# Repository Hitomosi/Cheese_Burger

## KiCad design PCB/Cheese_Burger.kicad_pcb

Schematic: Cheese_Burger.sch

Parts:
J1: BH-14SG; PinHeader_2x07_P2.54mm_Vertical

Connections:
3.3V: J1.13; also elsewhere on the board
3.3VA: J1.14; also elsewhere on the board
/IR_LED1/IR_LED_IN: J1.2; also elsewhere on the board
/IR_LED2/IR_LED_IN: J1.4; also elsewhere on the board
/IR_Sensor1/IR_SENSOR_OUT: J1.6; also elsewhere on the board
/IR_Sensor2/IR_SENSOR_OUT: J1.8; also elsewhere on the board
/IR_Sensor3/IR_SENSOR_OUT: J1.10; also elsewhere on the board
/IR_Sensor4/IR_SENSOR_OUT: J1.12; also elsewhere on the board
BATT: J1.1, J1.3, J1.5; also elsewhere on the board
GND: J1.7, J1.9, J1.11; also elsewhere on the board

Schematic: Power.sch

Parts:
C1: 10u; C_Disc_D5.0mm_W2.5mm_P5.00mm
C2: 0.1u; C_Disc_D5.0mm_W2.5mm_P5.00mm
D1: LED(OSNG5113A); LED_D5.0mm
F1: MF-RX160; RF-RX160
J2: JST_XA_1x2; JST_XH_B02B-XH-A_1x02_P2.50mm_Vertical
L1: 100u; L_Axial_L7.0mm_D3.3mm_P10.16mm_Horizontal_Fastron_MICC
Q1: 2SK4017; SIPAK_Vertical
R1: 100k; R_Axial_DIN0207_L6.3mm_D2.5mm_P7.62mm_Horizontal
R2: 68; R_Axial_DIN0207_L6.3mm_D2.5mm_P7.62mm_Horizontal
R3: 10; R_Axial_DIN0207_L6.3mm_D2.5mm_P7.62mm_Horizontal
R4, R5: 1k 1%; R_Axial_DIN0207_L6.3mm_D2.5mm_P7.62mm_Horizontal
SW1: SW_SPDT; PinHeader_1x03_P2.54mm_Vertical
U1: R-78E3.3-0.5; Converter_DCDC_RECOM_R-78E-0.5_THT

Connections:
1.65V: C2.1, R4.2, R5.1; also elsewhere on the board
3.3V: R2.1, R3.2, U1.3 (OUT); also elsewhere on the board
3.3VA: C1.1, L1.1, R4.1; also elsewhere on the board
BATT: Q1.2, U1.1 (IN); also elsewhere on the board
GND: C1.2, C2.2, D1.1, J2.2, R5.2, SW1.2, SW1.3, U1.2 (GND); also elsewhere on the board
unnamed: D1.2, R2.2
unnamed: F1.1, Q1.3, R1.1
unnamed: F1.2, J2.1
unnamed: L1.2, R3.1
unnamed: Q1.1, R1.2, SW1.1

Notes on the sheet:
11.1V

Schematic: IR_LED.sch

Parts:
D4, D5: LED_ALT; LED_D5.0mm_Horizontal_O6.35mm_Z9.0mm
Q3: 2SK2796; SIPAK_Vertical
R9: 10k; R_Axial_DIN0207_L6.3mm_D2.5mm_P7.62mm_Horizontal
R10: 10; R_Axial_DIN0207_L6.3mm_D2.5mm_P7.62mm_Horizontal
R11: 33 1/2W 1%; R_Axial_DIN0207_L6.3mm_D2.5mm_P7.62mm_Horizontal
U2: NJM2742D; DIP-8_W7.62mm_Socket

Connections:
/IR_LED1/IR_LED_IN: R9.2, U2.5; also elsewhere on the board
/IR_LED2/IR_LED_IN: U2.3; also elsewhere on the board
BATT: D4.2, U2.8; also elsewhere on the board
GND: R9.1, R11.1, U2.4; also elsewhere on the board
unnamed: D4.1, D5.2
unnamed: D5.1, Q3.2
unnamed 29: U2.2; also elsewhere on the board
unnamed: Q3.1, R10.1
unnamed: Q3.3, R11.2, U2.6
unnamed 32: U2.1; also elsewhere on the board
unnamed: R10.2, U2.7

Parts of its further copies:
D2, D3: LED_ALT; LED_D5.0mm_Horizontal_O6.35mm_Z9.0mm
Q2: 2SK2796; SIPAK_Vertical
R6: 10k; R_Axial_DIN0207_L6.3mm_D2.5mm_P7.62mm_Horizontal
R7: 10; R_Axial_DIN0207_L6.3mm_D2.5mm_P7.62mm_Horizontal
R8: 33 1/2W 1%; R_Axial_DIN0207_L6.3mm_D2.5mm_P7.62mm_Horizontal

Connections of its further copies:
/IR_LED2/IR_LED_IN: R6.2; also elsewhere on the board
BATT: D2.2; also elsewhere on the board
GND: R6.1, R8.1; also elsewhere on the board
unnamed: D2.1, D3.2
unnamed: D3.1, Q2.2
unnamed: Q2.1, R7.1
unnamed 29: Q2.3, R8.2; also elsewhere on the board
unnamed 32: R7.2; also elsewhere on the board

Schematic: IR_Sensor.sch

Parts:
C3, C4: 22p; C_Disc_D5.0mm_W2.5mm_P5.00mm
D6: D_Photo_ALT; LED_D5.0mm_Horizontal_O3.81mm_Z3.0mm
R12, R13: 220k; R_Axial_DIN0207_L6.3mm_D2.5mm_P7.62mm_Horizontal
U3: NJU7072D; DIP-8_W7.62mm_Socket

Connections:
1.65V: U3.3, U3.5; also elsewhere on the board
3.3VA: D6.1, U3.8; also elsewhere on the board
/IR_Sensor1/IR_SENSOR_OUT: C4.1, R13.1, U3.1; also elsewhere on the board
/IR_Sensor2/IR_SENSOR_OUT: U3.7; also elsewhere on the board
GND: R12.1, U3.4; also elsewhere on the board
unnamed: C3.1, C4.2, R13.2, U3.2
unnamed: C3.2, D6.2, R12.2
unnamed 13: U3.6; also elsewhere on the board

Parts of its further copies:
C5, C6, C7, C8, C9, C10: 22p; C_Disc_D5.0mm_W2.5mm_P5.00mm
D7, D8, D9: D_Photo_ALT; LED_D5.0mm_Horizontal_O3.81mm_Z3.0mm
R14, R15, R16, R17, R18, R19: 220k; R_Axial_DIN0207_L6.3mm_D2.5mm_P7.62mm_Horizontal
U4: NJU7072D; DIP-8_W7.62mm_Socket

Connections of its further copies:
1.65V: U4.3, U4.5; also elsewhere on the board
3.3VA: D7.1, D8.1, D9.1, U4.8; also elsewhere on the board
/IR_Sensor2/IR_SENSOR_OUT: C6.1, R15.1; also elsewhere on the board
/IR_Sensor3/IR_SENSOR_OUT: C8.1, R17.1, U4.1; also elsewhere on the board
/IR_Sensor4/IR_SENSOR_OUT: C10.1, R19.1, U4.7; also elsewhere on the board
GND: R14.1, R16.1, R18.1, U4.4; also elsewhere on the board
unnamed 13: C5.1, C6.2, R15.2; also elsewhere on the board
unnamed: C5.2, D7.2, R14.2
unnamed: C7.1, C8.2, R17.2, U4.2
unnamed: C7.2, D8.2, R16.2
unnamed: C9.2, D9.2, R18.2
unnamed: C9.1, C10.2, R19.2, U4.6

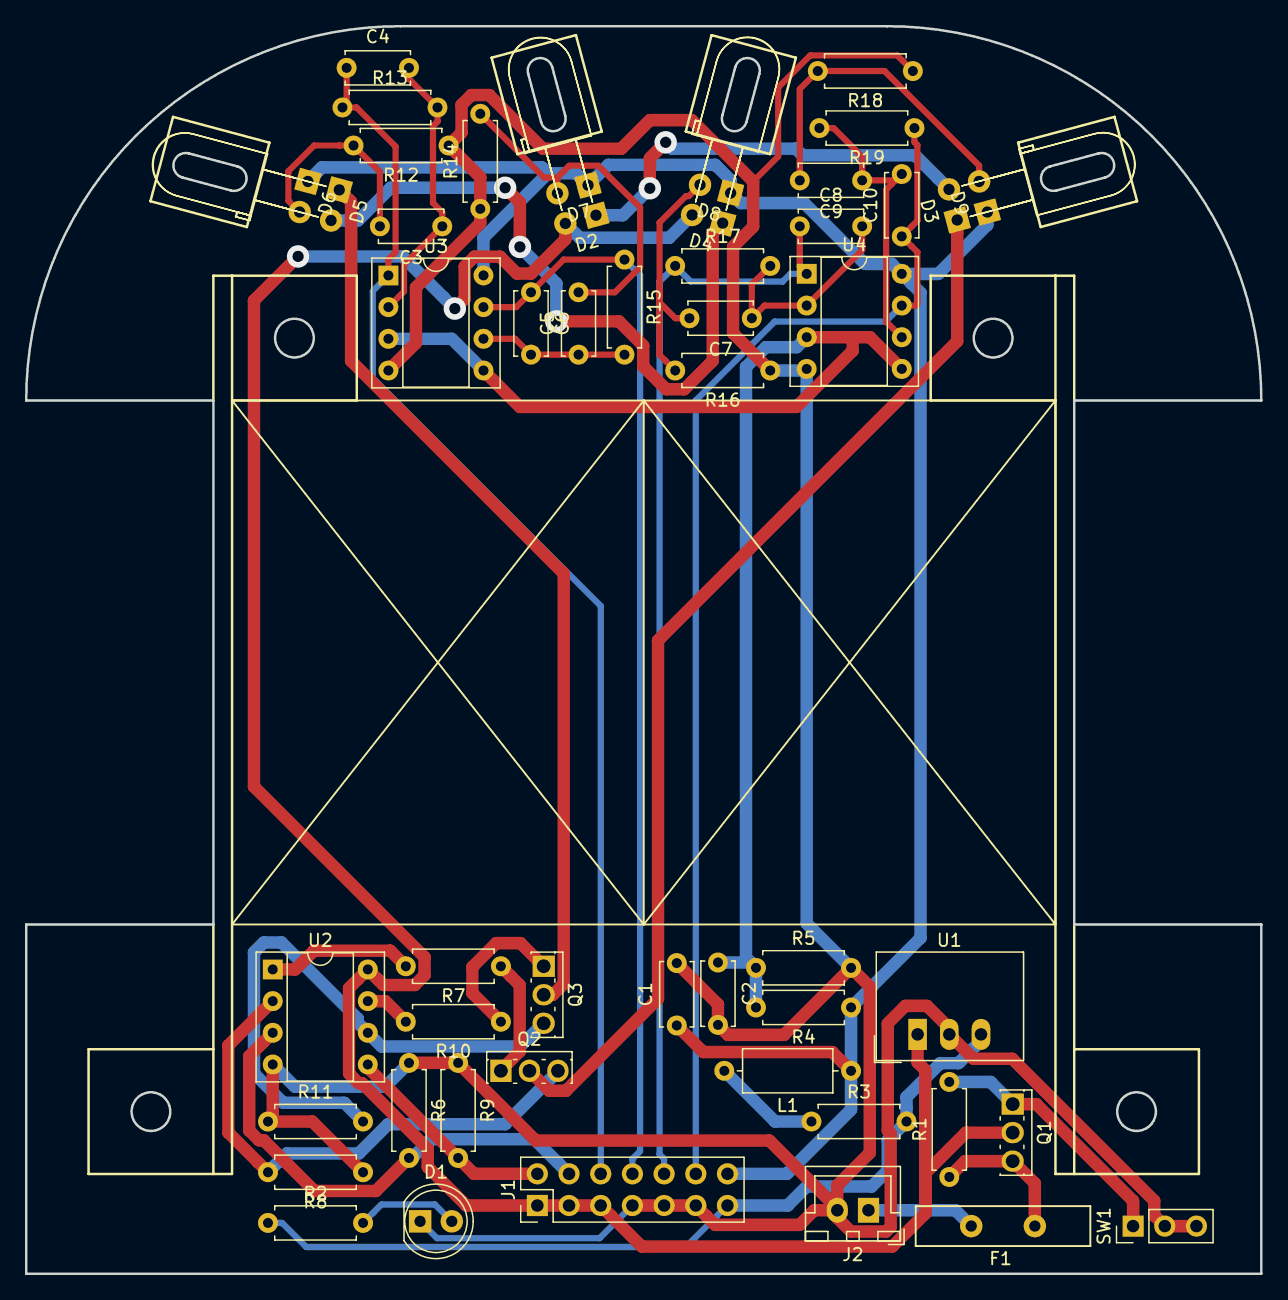
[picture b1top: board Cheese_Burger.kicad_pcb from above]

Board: 2 copper layers, 99.0 x 100.0 mm, 50 parts (0 on the bottom side), 34 nets.

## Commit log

2020-05-09 DXFを追加、部品配置を開始
2020-05-09 回路図を修正
2020-05-15 下側の基板の配線が終了
